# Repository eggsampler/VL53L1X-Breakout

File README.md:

# VL53L1X-Breakout

Minimal VL53L1X / VL53L1CX Breakout PCB developed in KiCad v6.

Images and schematic available in `etc` folder.

Manufacturing output files available in `outputs` folder. Generated with [KiKit](https://github.com/yaqwsx/KiKit) using:

`kikit fab jlcpcb --nametemplate VL53L1CX-Breakout-v2-{} --drc --assembly --schematic VL53L1CX-Breakout.kicad_sch --ignore J1 --field LCSC --corrections JLCPCB_CORRECTION VL53L1CX-Breakout.kicad_pcb outputs`

Approximate cost from JLCPCB for 5 assembled boards is $59 AUD excluding shipping.

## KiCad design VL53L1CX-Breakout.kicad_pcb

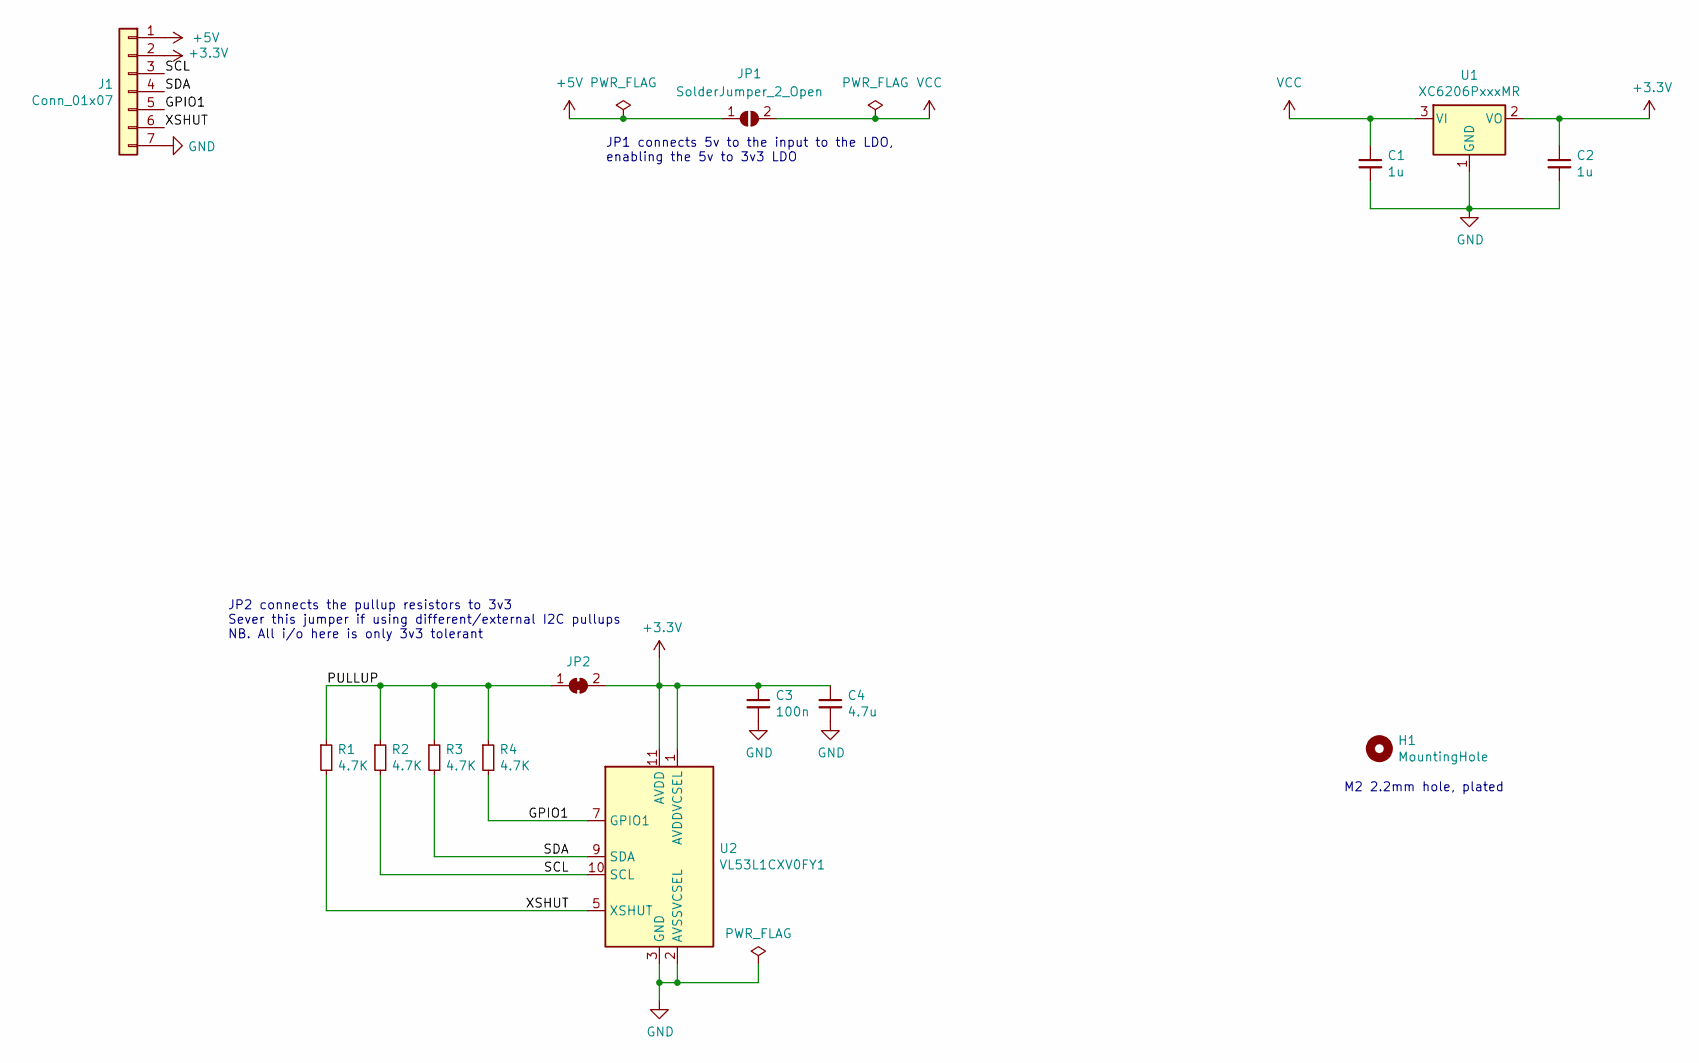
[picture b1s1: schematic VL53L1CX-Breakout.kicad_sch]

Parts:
C1, C2: 1u; C_0603_1608Metric; LCSC C15849
C3: 100n; C_0603_1608Metric; LCSC C14663
C4: 4.7u; C_0603_1608Metric; LCSC C19666
H1: MountingHole; MountingHole_2.2mm_M2_Pad_Via
J1: Conn_01x07; PinHeader_1x07_P2.54mm_Vertical
JP1: SolderJumper_2_Open; SolderJumper-2_P1.3mm_Open_RoundedPad1.0x1.5mm
JP2: SolderJumper_2_Bridged; SolderJumper-2_P1.3mm_Bridged_RoundedPad1.0x1.5mm
R1, R2, R3, R4: 4.7K; R_0603_1608Metric; LCSC C23162
U1: XC6206PxxxMR; SOT-23; LCSC C5446
U2: VL53L1CXV0FY1; ST_VL53L1x; LCSC C190004

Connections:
+3V3: C2.1, C3.1, C4.1, J1.2, JP2.2 (B), U1.2 (VO), U2.1 (AVDDVCSEL), U2.11 (AVDD)
+5V: J1.1, JP1.1 (A)
/GPIO1: J1.5, R4.2, U2.7 (GPIO1)
/PULLUP: JP2.1 (A), R1.1, R2.1, R3.1, R4.1
/SCL: J1.3, R2.2, U2.10 (SCL)
/SDA: J1.4, R3.2, U2.9 (SDA)
/XSHUT: J1.6, R1.2, U2.5 (XSHUT)
GND: C1.2, C2.2, C3.2, C4.2, J1.7, U1.1 (GND), U2.2 (AVSSVCSEL), U2.3 (GND), U2.4 (GND), U2.6 (GND), U2.12 (GND)
VCC: C1.1, JP1.2 (B), U1.3 (VI)

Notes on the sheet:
JP1 connects 5v to the input to the LDO, enabling the 5v to 3v3 LDO
JP2 connects the pullup resistors to 3v3 Sever this jumper if using different/external I2C pullups NB. All i/o here is only 3v3 tolerant
M2 2.2mm hole, plated

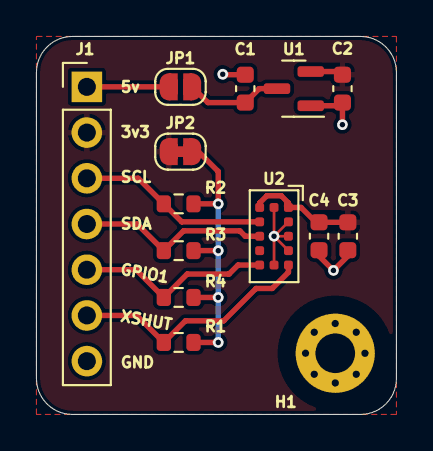
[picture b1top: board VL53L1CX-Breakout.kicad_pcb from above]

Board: 2 copper layers, 20.0 x 21.0 mm, 14 parts (0 on the bottom side), 9 nets.

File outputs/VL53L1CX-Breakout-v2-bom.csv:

Comment,Designator,Footprint,LCSC
1u,"C1,C2",Capacitor_SMD:C_0603_1608Metric, C15849
100n,C3,Capacitor_SMD:C_0603_1608Metric,C14663
4.7u,C4,Capacitor_SMD:C_0603_1608Metric,C19666
4.7K,"R1,R2,R3,R4",Resistor_SMD:R_0603_1608Metric,C23162
XC6206PxxxMR,U1,Package_TO_SOT_SMD:SOT-23,C5446
VL53L1CXV0FY1,U2,Sensor_Distance:ST_VL53L1x,C190004

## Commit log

2022-01-23 Commit v2 files
2022-01-23 Readme update, output regeneration.
